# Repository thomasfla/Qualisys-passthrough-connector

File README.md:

# Qualisys-passthrough-connector
PCB to create Qualisys connexion point that can be shunted by standard ethernet cable instead of long and expensive teconnectivity cloudsplitter cables (power + data)

Online viewer for this PCB: https://kicanvas.org/?github=https%3A%2F%2Fgithub.com%2Fthomasfla%2FQualisys-passthrough-connector

BOM:

* 2x https://www.mouser.fr/ProductDetail/TE-Connectivity-PB/2178126-1?qs=jA5Ki6243ol6GpSdLLgnTA%3D%3D
* 2x https://www.mouser.fr/ProductDetail/Amphenol-FCI/54602-908LF?qs=UB9wU2EYlYSRVSFArXBUoA%3D%3D
* 2x https://www.tme.eu/fr/details/xt30pw-m/connecteurs-dc/amass/

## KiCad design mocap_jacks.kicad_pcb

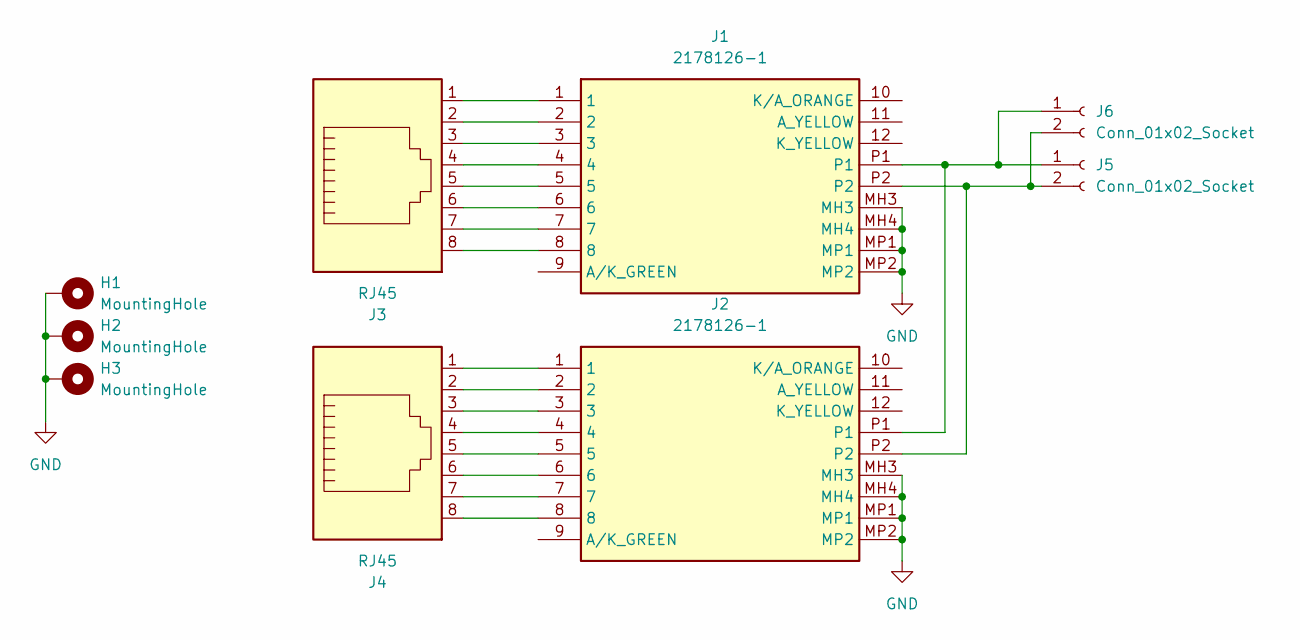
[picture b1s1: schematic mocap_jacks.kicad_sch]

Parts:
H1, H2, H3: MountingHole; MountingHole_2.5mm_Pad_Via
J1, J2: 2178126-1; 21781261; Mouser Part Number 571-2178126-1
J3, J4: RJ45; RJ45_Amphenol_54602-x08_Horizontal
J5, J6: Conn_01x02_Socket; AMASS_XT30PW-M_1x02_P2.50mm_Horizontal

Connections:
GND: H1.1, H2.1, H3.1, J1.MH3, J1.MH4, J1.MP1, J1.MP2, J2.MH3, J2.MH4, J2.MP1, J2.MP2
unnamed: J1.1, J3.1
unnamed: J1.2, J3.2
unnamed: J1.3, J3.3
unnamed: J1.4, J3.4
unnamed: J1.5, J3.5
unnamed: J1.6, J3.6
unnamed: J1.7, J3.7
unnamed: J1.8, J3.8
unnamed: J2.1, J4.1
unnamed: J2.2, J4.2
unnamed: J2.3, J4.3
unnamed: J2.4, J4.4
unnamed: J2.5, J4.5
unnamed: J2.6, J4.6
unnamed: J2.7, J4.7
unnamed: J2.8, J4.8
unnamed: J1.P1, J2.P1, J5.1, J6.1
unnamed: J1.P2, J2.P2, J5.2, J6.2

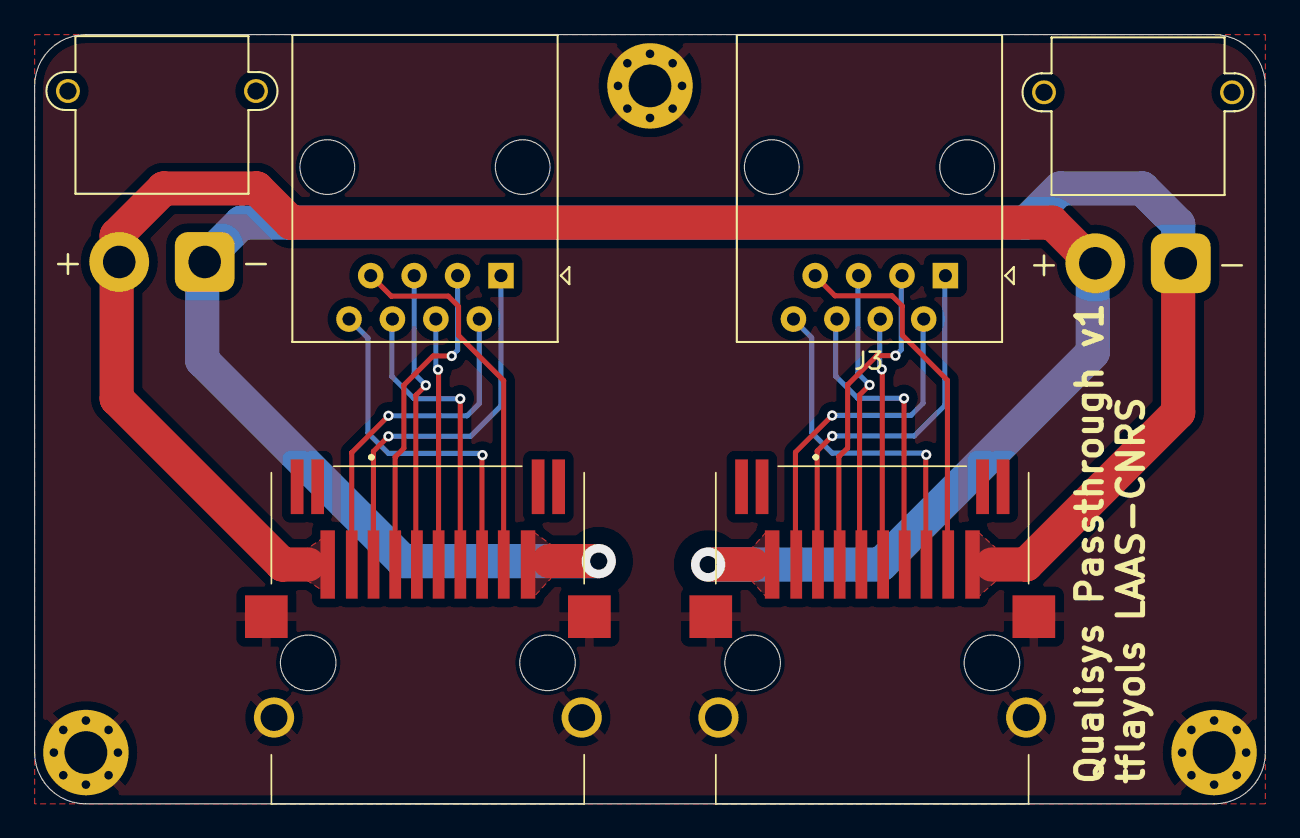
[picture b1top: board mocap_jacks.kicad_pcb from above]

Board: 2 copper layers, 72.0 x 45.0 mm, 9 parts (0 on the bottom side), 19 nets.

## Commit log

2025-02-18 add files
2025-02-18 add pcb file
